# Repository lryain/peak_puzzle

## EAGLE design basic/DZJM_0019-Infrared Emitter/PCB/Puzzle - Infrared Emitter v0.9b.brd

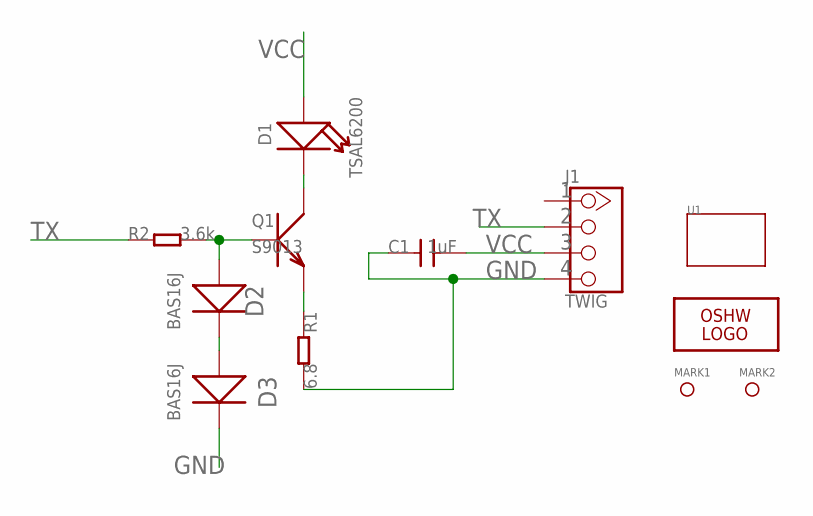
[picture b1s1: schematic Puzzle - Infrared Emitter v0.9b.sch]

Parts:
C1: 1uF; 0603
D1: TSAL6200; 2P-LEADED-ROUND-2.54-R3.0
D2, D3: BAS16J; D0805
J1: TWIG; 4P-LEADED-2.0
LOGO1: LOGO-OSHW-FILLX0150-NT; OSHW_FILLX150_NOTEXT
MARK1, MARK2: PAD-MARK; ROUND-MARK-0.635
Q1: S9013; SOT23
R1: 6.8; 0805
R2: 3.6k; 0603
U1: TWIG-1U; 1U-DIM-W/-DRILL

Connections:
GND: C1.1, D3.-, J1.4, R1.2
unnamed: D2.+, Q1.1 (B), R2.2
unnamed: D1.-, Q1.3 (C)
unnamed: Q1.2 (E), R1.1
unnamed: D2.-, D3.+
TX: J1.2, R2.1
VCC: C1.2, D1.+, J1.3

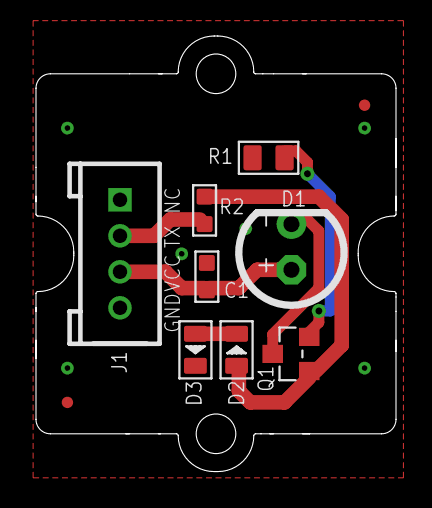
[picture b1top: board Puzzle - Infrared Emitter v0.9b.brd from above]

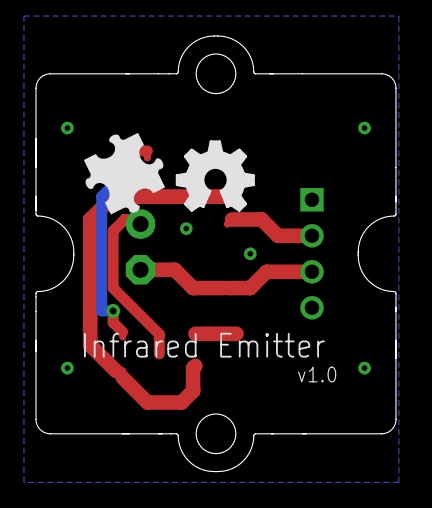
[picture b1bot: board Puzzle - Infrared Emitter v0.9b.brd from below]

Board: 2 copper layers, 20.0 x 24.2 mm, 13 parts (2 on the bottom side), 7 nets.

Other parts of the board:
U$2: BRICK-LOGO-MIL-0.5

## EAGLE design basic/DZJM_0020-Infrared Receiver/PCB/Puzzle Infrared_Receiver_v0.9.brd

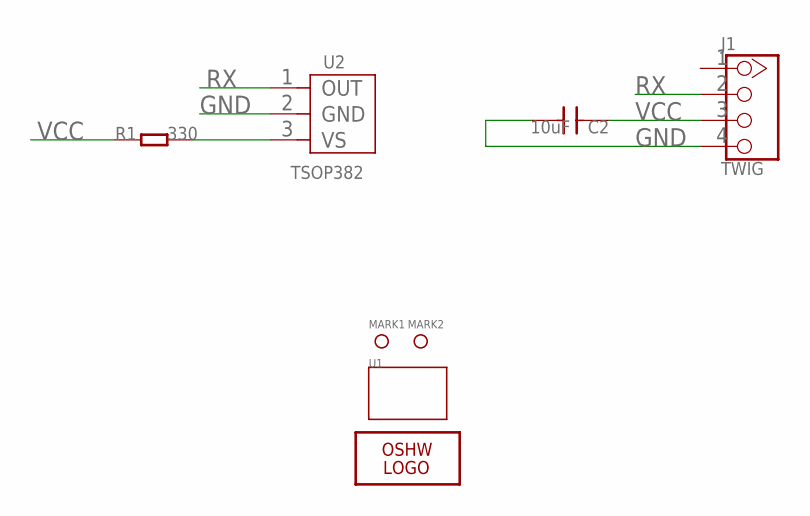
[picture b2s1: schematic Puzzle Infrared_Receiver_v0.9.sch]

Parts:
C2: 10uF; 0805
J1: TWIG; 4P-LEADED-2.0
LOGO1: LOGO-OSHW-FILLX0150-NT; OSHW_FILLX150_NOTEXT
MARK1, MARK2: PAD-MARK; ROUND-MARK-0.635
R1: 330; 0603
U1: TWIG-1U; 1U-DIM-W/-DRILL
U2: TSOP382; 3P-2.54-4.8X5X6.95H

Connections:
GND: J1.4, U2.2 (GND)
unnamed: R1.2, U2.3 (VS)
RX: J1.2, U2.1 (OUT)
VCC: C2.1, J1.3, R1.1

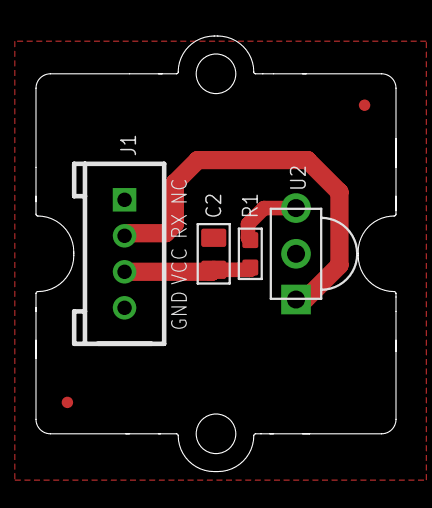
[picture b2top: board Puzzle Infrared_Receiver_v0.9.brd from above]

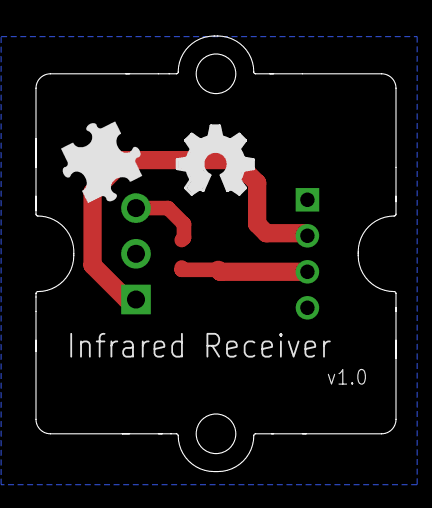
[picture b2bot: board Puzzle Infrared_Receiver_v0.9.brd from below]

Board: 2 copper layers, 20.0 x 24.2 mm, 9 parts (2 on the bottom side), 4 nets.

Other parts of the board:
U$2: BRICK-LOGO-MIL-0.5

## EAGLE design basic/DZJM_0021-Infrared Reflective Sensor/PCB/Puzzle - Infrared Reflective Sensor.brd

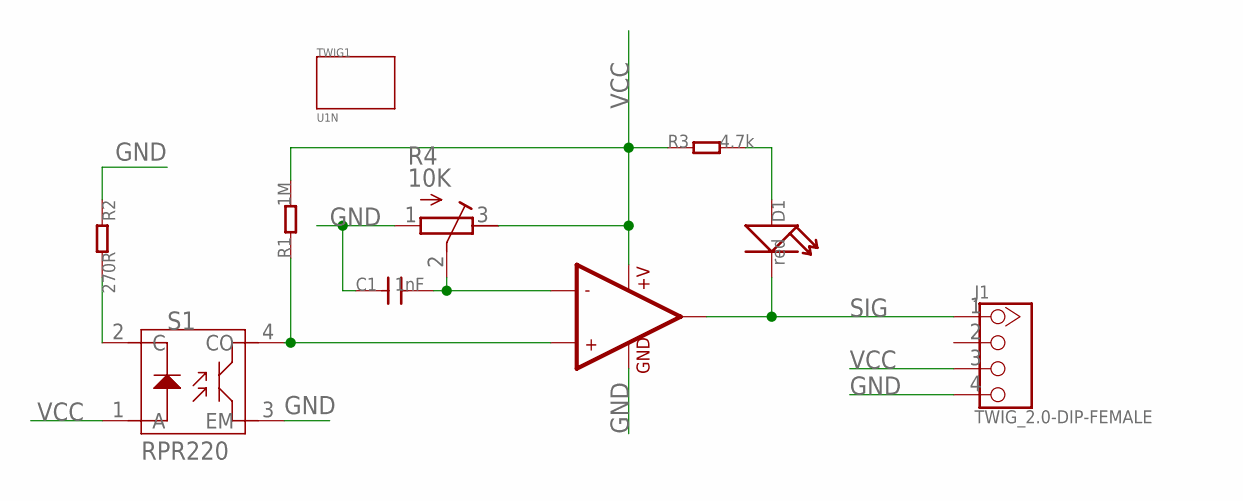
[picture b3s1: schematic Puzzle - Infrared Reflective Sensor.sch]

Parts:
C1: 1nF; 0603
D1: red; LED0603
J1: TWIG_2.0-DIP-FEMALE; 2.0_1X4
R1: 1M; 0603_S
R2: 270R; 0603_S
R3: 4.7k; 0603_S
R4: 10K; RTRIM3214W
S1: RPR220; 4P-6.4X4.9X6.5H
TWIG1: U1N
U1: 002-LMV358; SO08

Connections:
GND: C1.1, J1.4, R2.1, R4.1 (E), S1.3 (EM), U1.4 (GND)
unnamed: C1.2, R4.2 (S), U1.2 (-IN1)
unnamed: R1.1, S1.4 (CO), U1.3 (+IN1)
unnamed: R2.2, S1.2 (C)
unnamed: D1.1 (+), R3.2
SIG: D1.2 (-), J1.1, U1.1 (OUT1)
VCC: J1.3, R1.2, R3.1, R4.3 (A), S1.1 (A), U1.8 (+V)

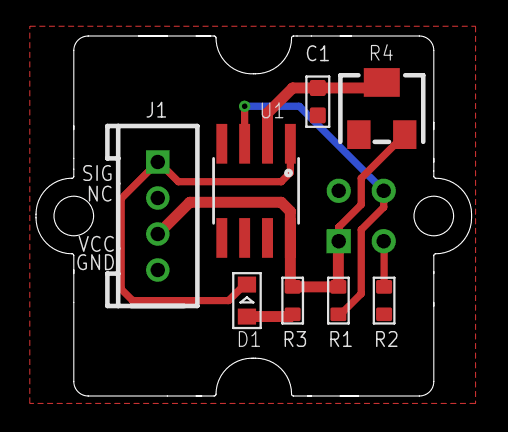
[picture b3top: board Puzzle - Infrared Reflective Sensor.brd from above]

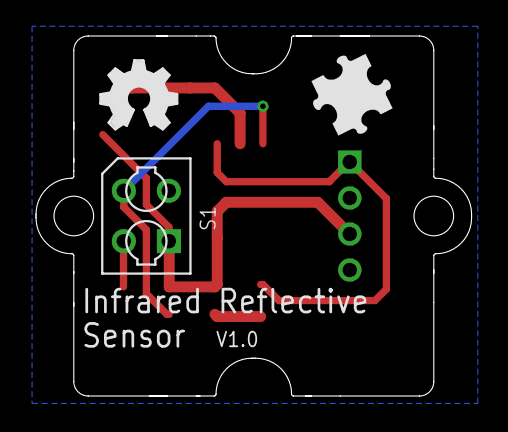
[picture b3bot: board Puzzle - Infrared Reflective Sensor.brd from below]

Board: 2 copper layers, 24.2 x 20.0 mm, 12 parts (3 on the bottom side), 7 nets.

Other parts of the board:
U$1: OSHW_FILLX150_NOTEXT
U$2: BRICK-LOGO-MIL-0.5

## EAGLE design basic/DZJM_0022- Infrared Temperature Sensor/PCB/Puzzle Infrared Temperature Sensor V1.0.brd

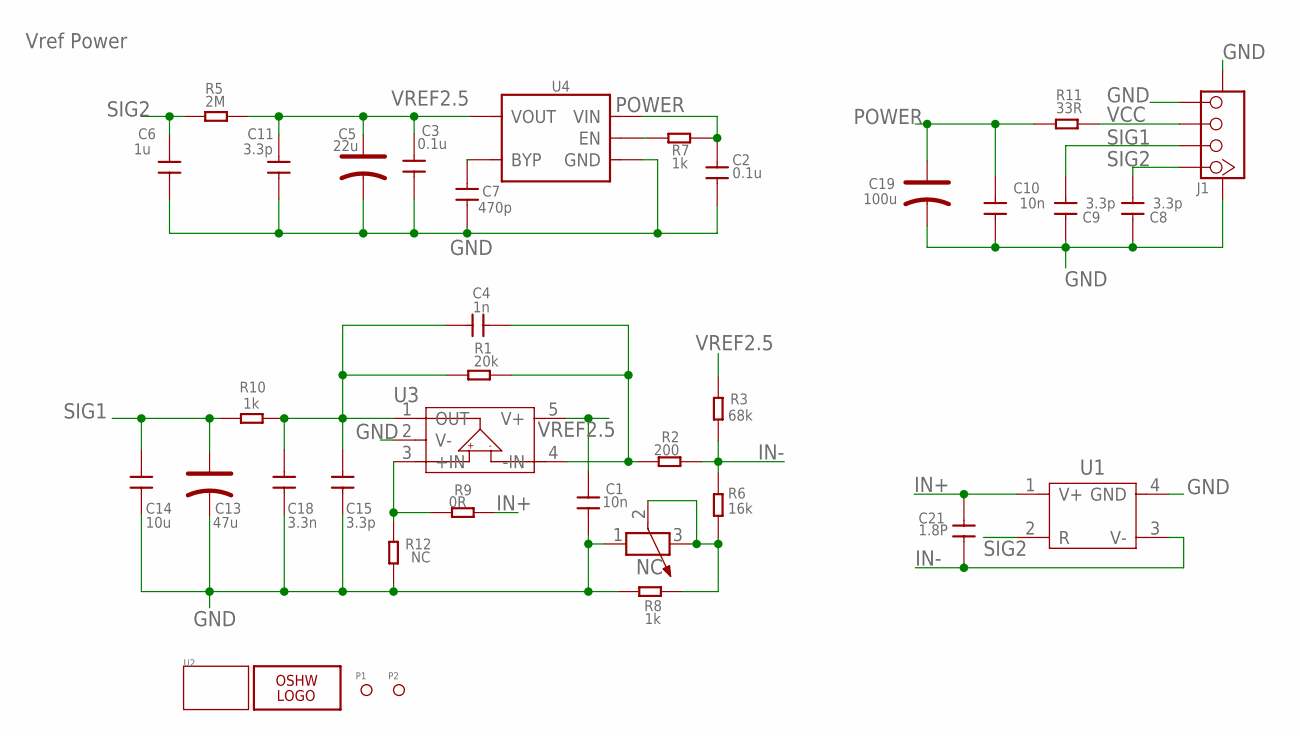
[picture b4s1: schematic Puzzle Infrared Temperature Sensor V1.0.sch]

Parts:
C1: 10n; 0603
C2, C3: 0.1u; 0402
C4: 1n; 0603
C5: 22u; AVX-A
C6: 1u; 0603
C7: 470p; 0402
C8, C9, C11: 3.3p; 0402
C10: 10n; 0402
C13: 47u; AVX-A
C14: 10u; 0603
C15: 3.3p; 0603
C18: 3.3n; 0603
C19: 100u; AVX-B
C21: 1.8P; 0603
J1: TWIG-4P-2.0-SMD-FEMALE-REINFORCE'90D'; 4P-SMD-2.0-90D
LOGO1: LOGO-OSHW-6MILX0200-NT; OSHW_6X200_NOTEXT
P1, P2: PAD-MARK; ROUND-MARK-0.635
R1: 20k; 0603
R2: 200; 0603
R3: 68k; 0603
R4: NC; 3P-SMD-SQUA-3.6X3.3
R5: 2M; 0402
R6: 16k; 0603
R7: 1k; 0402
R8, R10: 1k; 0603
R9: 0R; 0603
R11: 33R; 0402
R12: NC; 0603
U1: SENSOR-OTP-538U; 4P-5.4MM
U2: TWIG-2U; 2U-DIM-W/-DRILL
U3: OPA333; SOT23-5
U4: MIC5205; SOT23-5

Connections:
GND: C1.2, C2.2, C3.2, C5.-, C6.2, C7.2, C8.2, C9.2, C10.2, C11.2, C13.-, C14.2, C15.2, C18.2, C19.-, J1.4, J1.SS1, J1.SS2, R4.1, R8.1, R12.1, U1.4 (GND), U3.2 (V-), U4.2 (GND)
IN+: C21.2, R9.1, U1.1 (V+)
IN-: C21.1, R2.1, R3.2, R6.1, U1.3 (V-)
unnamed: C4.2, R1.1, R2.2, U3.4 (-IN)
unnamed: R4.2 (3), R4.3 (2), R6.2, R8.2
unnamed: R7.1, U4.3 (EN)
unnamed: R9.2, R12.2, U3.3 (+IN)
unnamed: C7.1, U4.4 (BYP)
unnamed: C4.1, C15.1, C18.1, R1.2, R10.1, U3.1 (OUT)
POWER: C2.1, C10.1, C19.+, R7.2, R11.1, U4.1 (VIN)
SIG1: C9.1, C13.+, C14.1, J1.2, R10.2
SIG2: C6.1, C8.1, J1.1, R5.1, U1.2 (R)
VCC: J1.3, R11.2
VREF2.5: C1.1, C3.1, C5.+, C11.1, R3.1, R5.2, U3.5 (V+), U4.5 (VOUT)

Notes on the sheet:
Vref Power

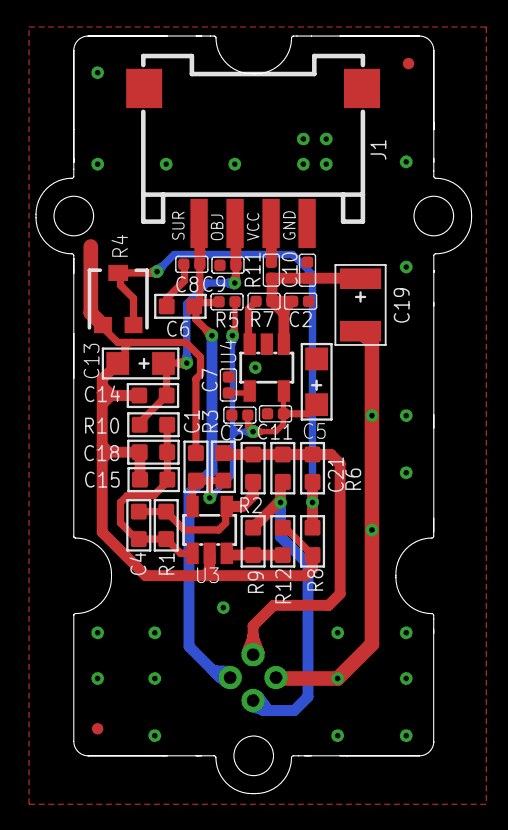
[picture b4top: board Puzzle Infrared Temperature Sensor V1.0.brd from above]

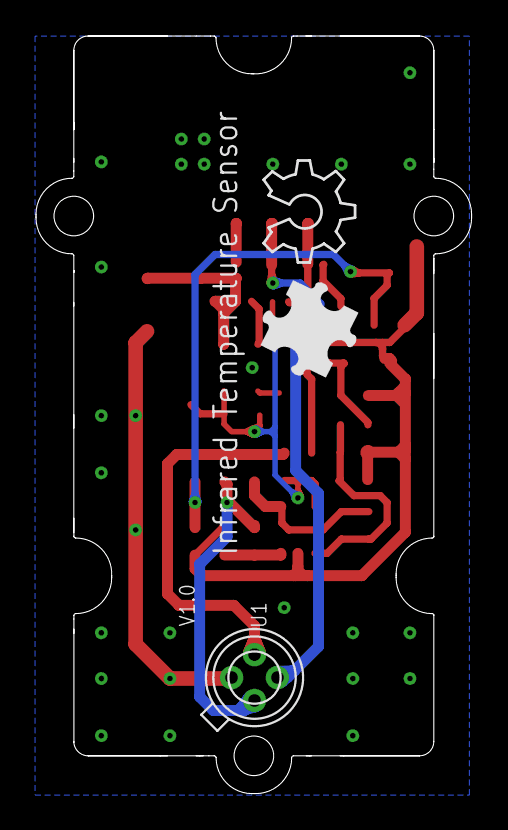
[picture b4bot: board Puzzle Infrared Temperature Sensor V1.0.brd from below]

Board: 2 copper layers, 24.2 x 42.1 mm, 38 parts (2 on the bottom side), 14 nets.

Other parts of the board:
U$1: BRICK-LOGO-2-B-MIL-0.6

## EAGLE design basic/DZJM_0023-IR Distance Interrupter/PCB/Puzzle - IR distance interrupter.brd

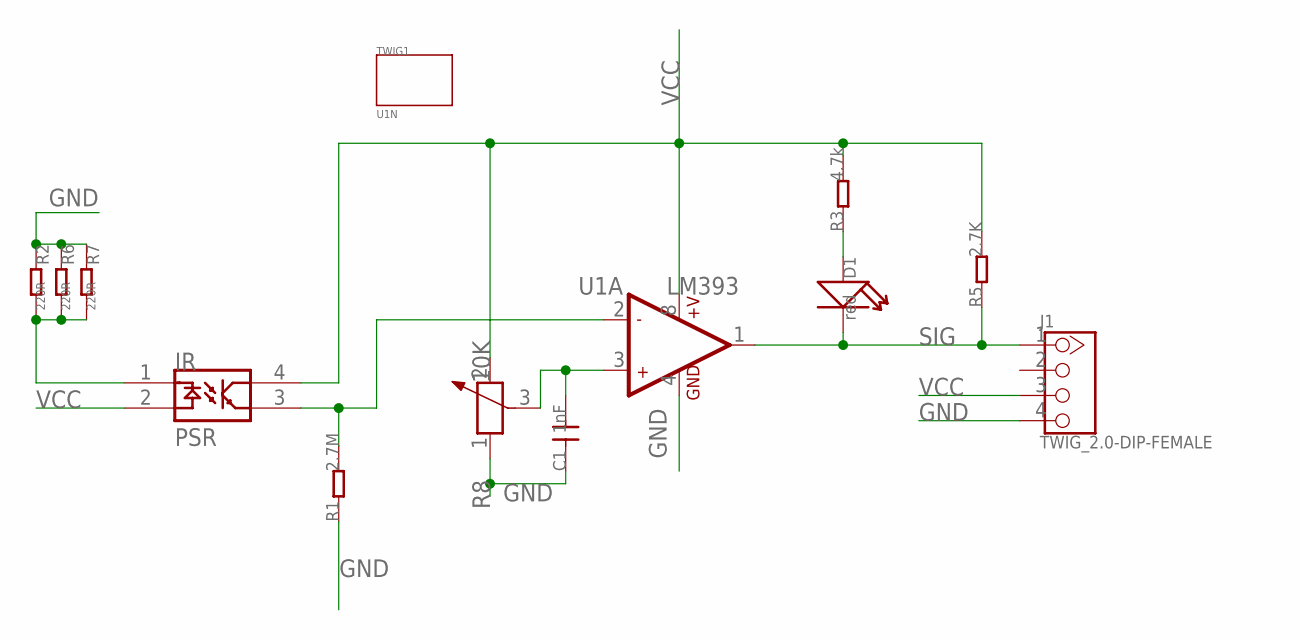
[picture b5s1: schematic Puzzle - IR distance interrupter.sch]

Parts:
C1: 1nF; 0603
D1: red; LED0603
J1: TWIG_2.0-DIP-FEMALE; 2.0_1X4
PSR: PSR
R1: 2.7M; 0603_S
R2, R6, R7: 220R; 0805
R3: 4.7k; 0603_S
R5: 2.7K; 0603_S
R8: 10K; 3P-SQUA-7X6.8
TWIG1: U1N
U1: LM393; SO08

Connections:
GND: C1.1, J1.4, R1.1, R2.1, R6.1, R7.1, R8.1, U1.4 (GND)
unnamed: C1.2, R8.3, U1.3 (+IN1)
unnamed: D1.1 (+), R3.1
unnamed: PSR.3, R1.2, U1.2 (-IN1)
unnamed: PSR.1, R2.2, R6.2, R7.2
SIG: D1.2 (-), J1.1, R5.1, U1.1 (OUT1)
VCC: J1.3, PSR.2, PSR.4, R3.2, R5.2, R8.2, U1.8 (+V)

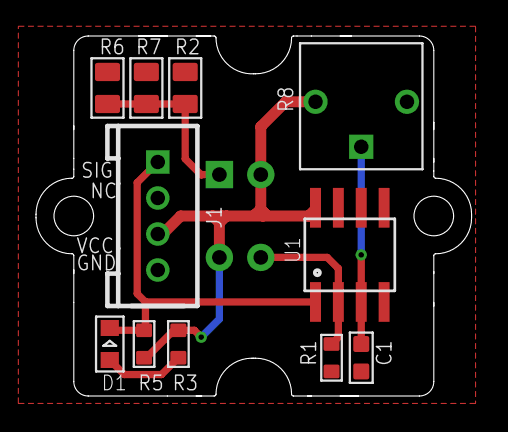
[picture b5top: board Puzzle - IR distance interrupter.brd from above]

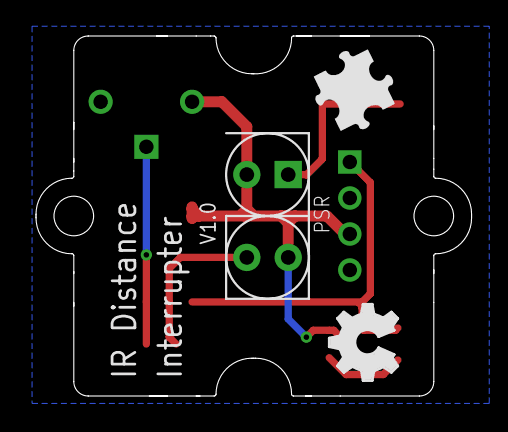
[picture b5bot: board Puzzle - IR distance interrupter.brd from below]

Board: 2 copper layers, 24.2 x 20.0 mm, 15 parts (3 on the bottom side), 7 nets.

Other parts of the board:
U$1: OSHW_FILLX150_NOTEXT
U$2: BRICK-LOGO-MIL-0.5

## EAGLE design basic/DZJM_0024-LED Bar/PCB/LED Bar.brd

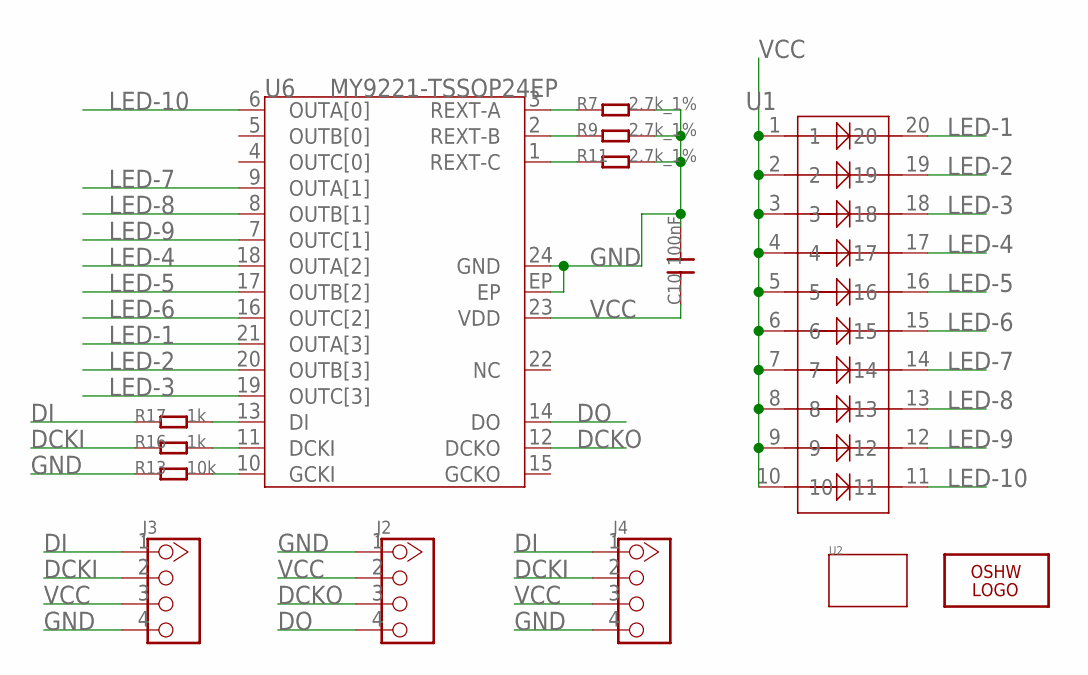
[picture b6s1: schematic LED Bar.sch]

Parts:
C10: 100nF; 0603
J2: HEADER-4P-90D; 4P-2.54-90
J3: HEADER-4P'2.54-90D-FEMALE'; 4P-2.54-90D-FEMALE
J4: TWIG-4P-2.0-2.0; 4P-2.0
LOGO1: LOGO-OSHW-FILLX0150-NT; OSHW_FILLX150_NOTEXT
R7, R9, R11: 2.7k_1%; 0603
R13: 10k; 0603
R16, R17: 1k; 0603
U1: LED-20P; 20P-DIP-2.54-25.5X10.1X8.4H
U2: TWIG-2U; 2U-DIM-W/-DRILL
U6: MY9221-TSSOP24EP; TSSOP24EP

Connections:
DCKI: J3.2, J4.2, R16.1
DCKO: J2.3, U6.12 (DCKO)
DI: J3.1, J4.1, R17.1
DO: J2.4, U6.14 (DO)
GND: C10.2, J2.1, J3.4, J4.4, R7.2, R9.2, R11.2, R13.1, U6.24 (GND), U6.EP
LED-1: U1.20, U6.21 (OUTA[3])
LED-2: U1.19, U6.20 (OUTB[3])
LED-3: U1.18, U6.19 (OUTC[3])
LED-4: U1.17, U6.18 (OUTA[2])
LED-5: U1.16, U6.17 (OUTB[2])
LED-6: U1.15, U6.16 (OUTC[2])
LED-7: U1.14, U6.9 (OUTA[1])
LED-8: U1.13, U6.8 (OUTB[1])
LED-9: U1.12, U6.7 (OUTC[1])
LED-10: U1.11, U6.6 (OUTA[0])
unnamed: R17.2, U6.13 (DI)
unnamed: R16.2, U6.11 (DCKI)
unnamed: R13.2, U6.10 (GCKI)
unnamed: R11.1, U6.1 (REXT-C)
unnamed: R9.1, U6.2 (REXT-B)
unnamed: R7.1, U6.3 (REXT-A)
VCC: C10.1, J2.2, J3.3, J4.3, U1.1, U1.2, U1.3, U1.4, U1.5, U1.6, U1.7, U1.8, U1.9, U1.10, U6.23 (VDD)

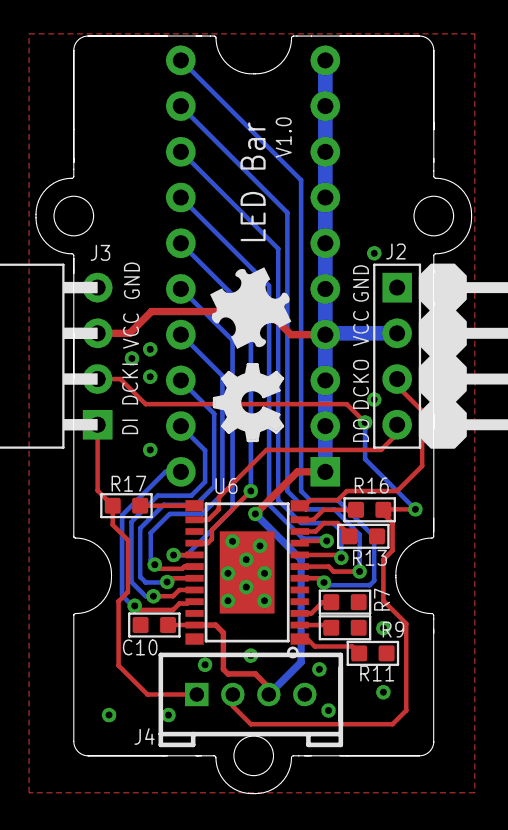
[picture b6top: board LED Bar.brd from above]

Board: 2 copper layers, 24.2 x 42.1 mm, 15 parts (1 on the bottom side), 22 nets.

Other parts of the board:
U$2: BRICK-LOGO-MIL-0.5

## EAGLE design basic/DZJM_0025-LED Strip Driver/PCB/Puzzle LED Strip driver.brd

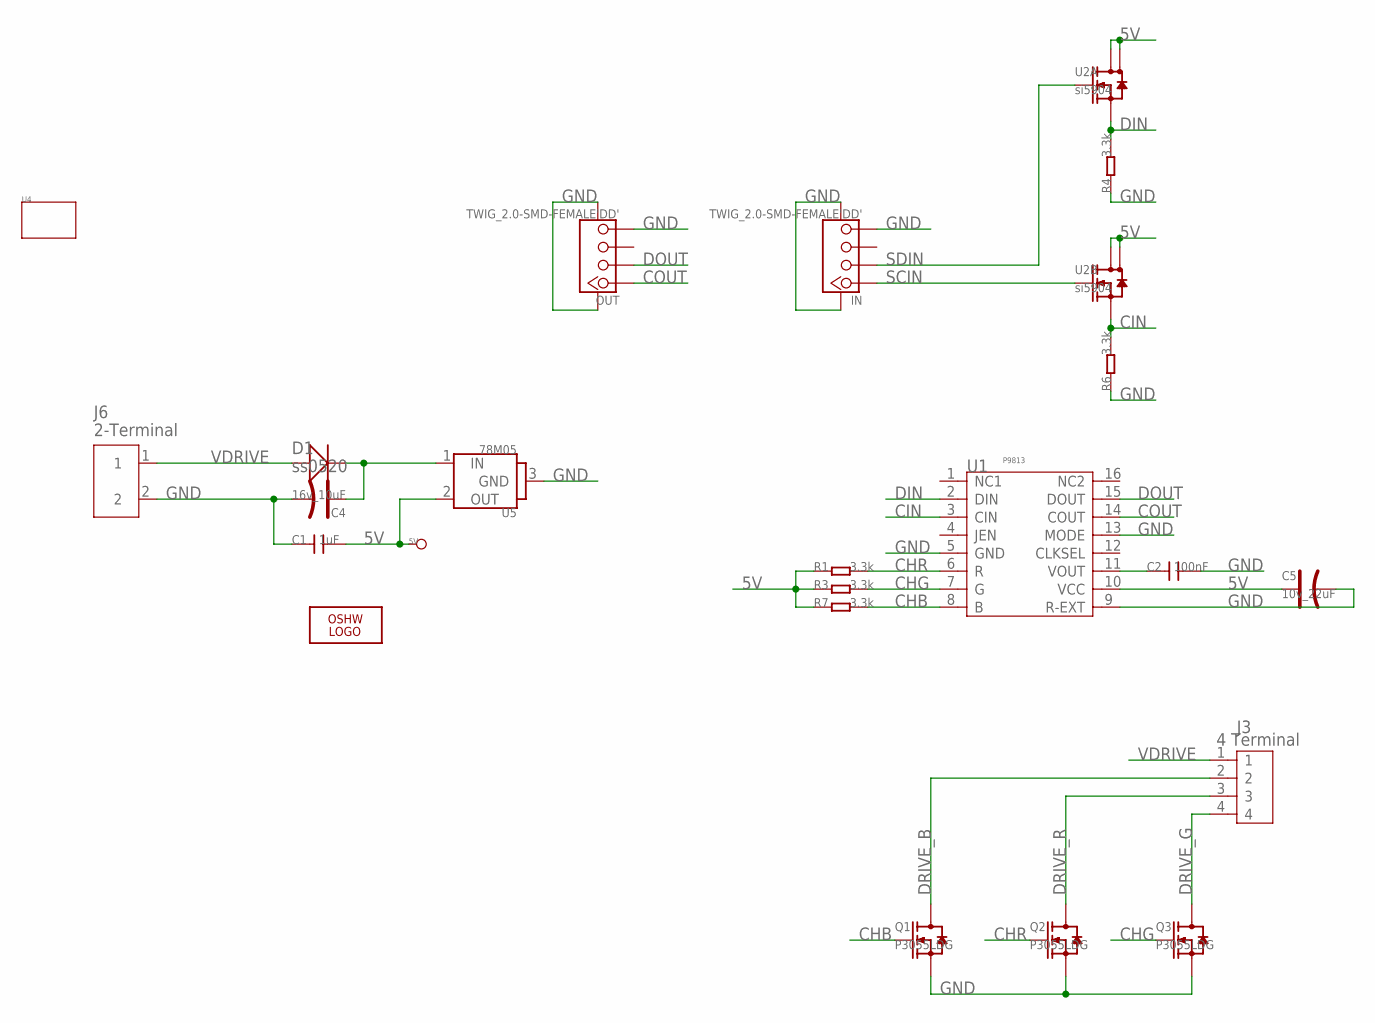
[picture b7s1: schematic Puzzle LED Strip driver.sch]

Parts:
5V: DNP; TP_3535
C1: 1uF; 0805
C2: 100nF; 0402
C4: 16v_10uF; AVX-A
C5: 10v_22uF; AVX-A
D1: ss0520; SOD123
IN: TWIG_2.0-SMD-FEMALE'DD'; 2.0_1X4DD
J3: 4 Terminal; 4P-3.36
J6: 2-Terminal; 2P-3.36
LOGO1: LOGO-OSHW-FILLX0200-NT; OSHW_FILLX200_NOTEXT
OUT: TWIG_2.0-SMD-FEMALE'DD'; 2.0_1X4DD
Q1, Q2, Q3: P3055LDG; TO252
R1, R3, R4, R6, R7: 3.3k; 0402
U1: P9813; SSOP16
U2: si5904; 1206-8
U4: TWIG3U-W/O-DRILL; 3U-DIM-W/O-DRILL
U5: 78M05; TO252

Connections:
5V: 5V.T, C1.2, C5.+, R1.1, R3.1, R7.1, U1.10 (VCC), U2.5 (D), U2.6 (D), U2.7 (D), U2.8 (D), U5.2 (OUT)
CHB: Q1.1 (G), R7.2, U1.8 (B)
CHG: Q3.1 (G), R3.2, U1.7 (G)
CHR: Q2.1 (G), R1.2, U1.6 (R)
CIN: R6.2, U1.3 (CIN), U2.3 (S)
COUT: OUT.1, U1.14 (COUT)
DIN: R4.2, U1.2 (DIN), U2.1 (S)
DOUT: OUT.2, U1.15 (DOUT)
DRIVE_B: J3.2, Q1.2 (D)
DRIVE_G: J3.4, Q3.2 (D)
DRIVE_R: J3.3, Q2.2 (D)
GND: C1.1, C2.2, C4.-, C5.-, IN.4, IN.SS1, IN.SS2, J6.2, OUT.4, OUT.SS1, OUT.SS2, Q1.3 (S), Q2.3 (S), Q3.3 (S), R4.1, R6.1, U1.5 (GND), U1.9 (R-EXT), U1.13 (MODE), U5.3 (GND)
unnamed: C2.1, U1.11 (VOUT)
unnamed: C4.+, D1.-, U5.1 (IN)
SCIN: IN.1, U2.4 (G)
SDIN: IN.2, U2.2 (G)
VDRIVE: D1.+, J3.1, J6.1

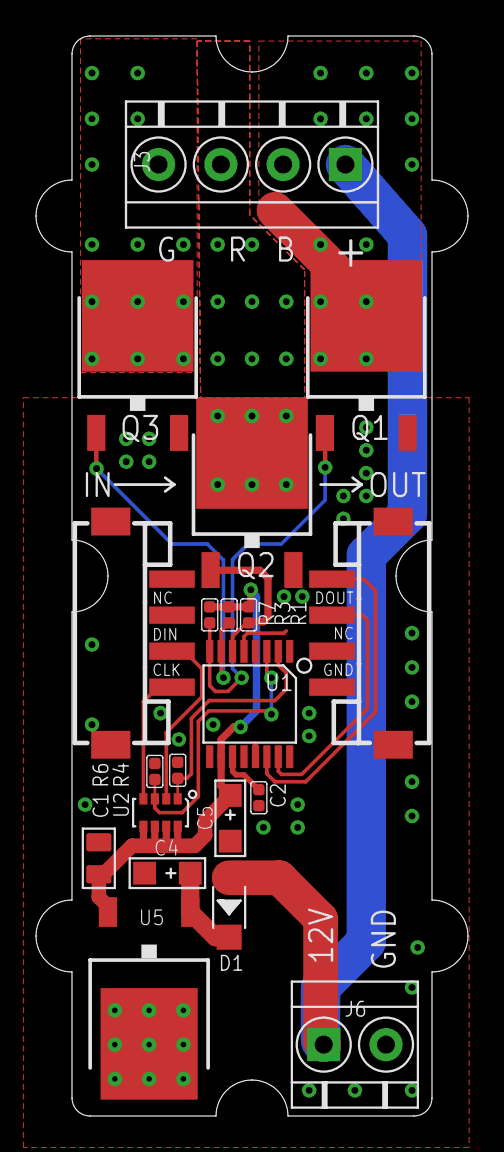
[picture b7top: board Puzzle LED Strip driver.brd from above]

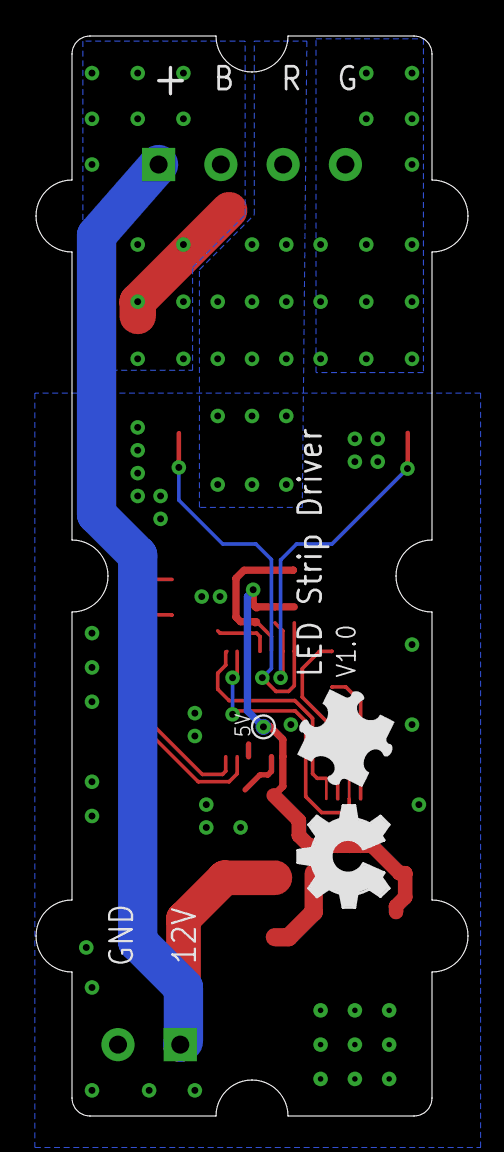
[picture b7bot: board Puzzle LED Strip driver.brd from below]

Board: 2 copper layers, 24.0 x 60.0 mm, 24 parts (2 on the bottom side), 17 nets.

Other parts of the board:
U$2: BRICK-LOGO-2-B-MIL-0.6
